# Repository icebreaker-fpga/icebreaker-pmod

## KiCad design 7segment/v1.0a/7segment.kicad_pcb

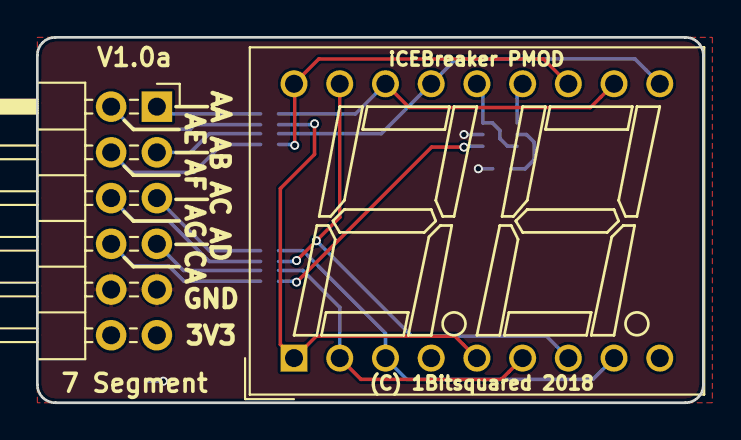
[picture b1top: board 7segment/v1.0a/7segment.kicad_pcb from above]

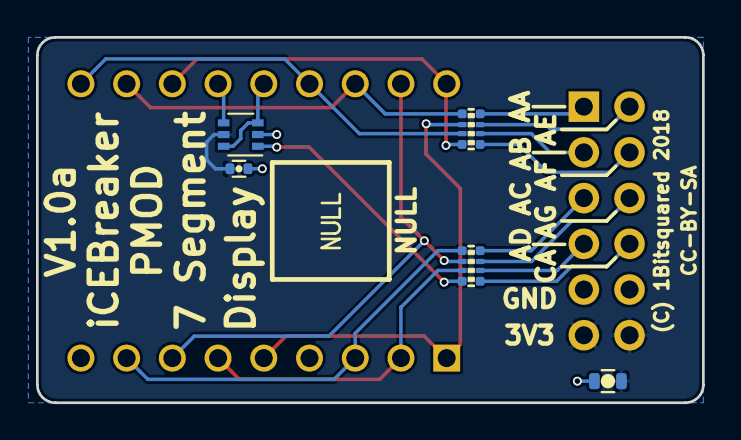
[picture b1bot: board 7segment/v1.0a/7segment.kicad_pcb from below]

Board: 2 copper layers, 37.0 x 20.3 mm, 7 parts (5 on the bottom side), 20 nets.

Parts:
C1: 10u; C_0603
C2: 100n; C_0402
J1: PMOD; PMODHeader_2x06_P2.54mm_Horizontal
R1, R2: 330E; R_Array_Convex_4x0402
U1: LTD-6910HR
U2: NL27WZ14; SOT-363_SC-70-6

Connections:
+3V3: C1.1, C2.1, J1.6, J1.12, U2.5
/AA: J1.1, R2.2
/AAx: R2.1, U1.11, U1.16
/AB: J1.2, R2.6
/ABx: R2.5, U1.10, U1.15
/AC: J1.3, R1.2
/ACx: R1.1, U1.3, U1.8
/AD: J1.4, R1.6
/ADx: R1.5, U1.2, U1.6
/AE: J1.7, R2.4
/AEx: R2.3, U1.1, U1.5
/AF: J1.8, R2.8
/AFx: R2.7, U1.12, U1.18
/AG: J1.9, R1.4
/AGx: R1.3, U1.7, U1.17
/CAT: J1.10, R1.8
/CAT1: U1.14, U2.3, U2.6
/CAT2: U1.13, U2.4
/CATx: R1.7, U2.1
GND: C1.2, C2.2, J1.5, J1.11, U2.2

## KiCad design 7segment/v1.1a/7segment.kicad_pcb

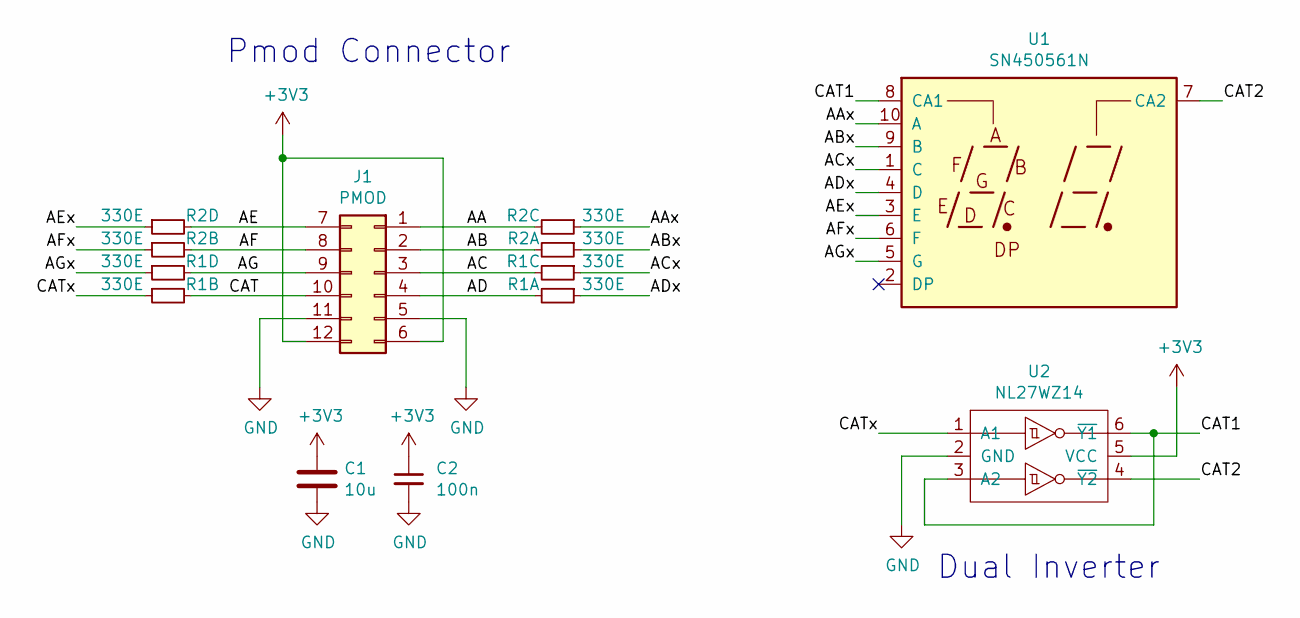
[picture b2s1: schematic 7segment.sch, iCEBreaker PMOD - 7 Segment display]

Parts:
C1: 10u; C_0603
C2: 100n; C_0402
J1: PMOD; PMODHeader_2x06_P2.54mm_Horizontal
R1, R2: 330E; R_Array_Convex_4x0402
U1: SN450561N
U2: NL27WZ14; SOT-363_SC-70-6

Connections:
+3V3: C1.1, C2.1, J1.6, J1.12, U2.5 (VCC)
/AA: J1.1, R2.6
/AAx: R2.5, U1.10 (A)
/AB: J1.2, R2.2
/ABx: R2.1, U1.9 (B)
/AC: J1.3, R1.6
/ACx: R1.5, U1.1 (C)
/AD: J1.4, R1.2
/ADx: R1.1, U1.4 (D)
/AE: J1.7, R2.8
/AEx: R2.7, U1.3 (E)
/AF: J1.8, R2.4
/AFx: R2.3, U1.6 (F)
/AG: J1.9, R1.8
/AGx: R1.7, U1.5 (G)
/CAT: J1.10, R1.4
/CAT1: U1.8 (CA1), U2.3 (A2), U2.6 (~Y1)
/CAT2: U1.7 (CA2), U2.4 (~Y2)
/CATx: R1.3, U2.1 (A1)
GND: C1.2, C2.2, J1.5, J1.11, U2.2 (GND)

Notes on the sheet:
Dual Inverter
Pmod Connector

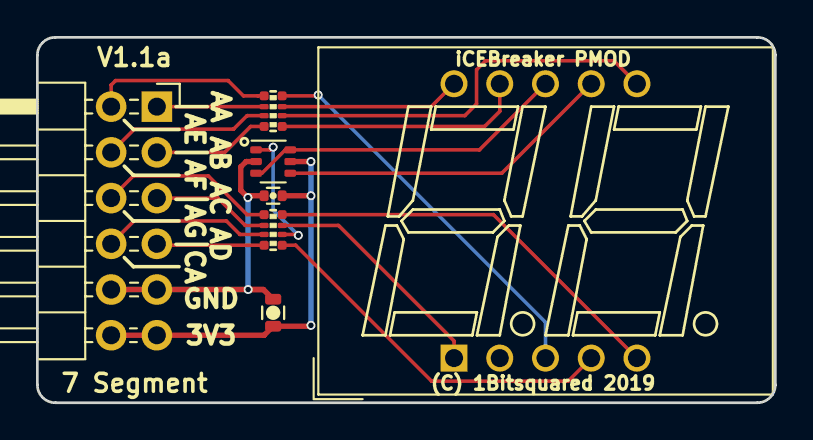
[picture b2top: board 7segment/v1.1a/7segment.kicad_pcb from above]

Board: 2 copper layers, 41.0 x 20.3 mm, 7 parts (0 on the bottom side), 20 nets.

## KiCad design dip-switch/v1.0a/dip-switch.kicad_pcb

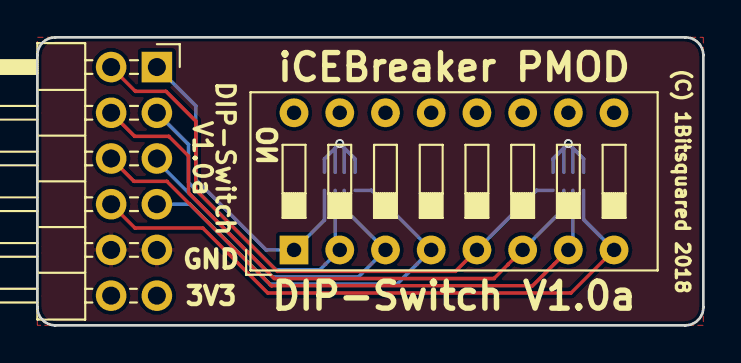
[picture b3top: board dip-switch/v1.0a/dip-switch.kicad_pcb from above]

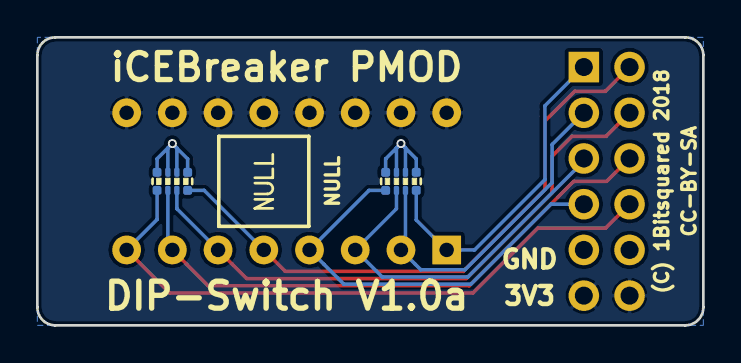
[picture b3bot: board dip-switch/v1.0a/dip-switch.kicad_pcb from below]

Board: 2 copper layers, 37.0 x 16.0 mm, 4 parts (2 on the bottom side), 10 nets.

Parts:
J1: PMOD; PMODHeader_2x06_P2.54mm_Horizontal
R1, R2: 10k; R_Array_Convex_4x0402
SW1: SW_DIP_x08; SW_DIP_SPSTx08_Slide_9.78x22.5mm_W7.62mm_P2.54mm

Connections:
+3V3: J1.6, J1.12, SW1.9, SW1.10, SW1.11, SW1.12, SW1.13, SW1.14, SW1.15, SW1.16
/DIP1: J1.1, R1.2, SW1.1
/DIP2: J1.2, R1.4, SW1.2
/DIP3: J1.3, R1.6, SW1.3
/DIP4: J1.4, R1.8, SW1.4
/DIP5: J1.7, R2.2, SW1.5
/DIP6: J1.8, R2.4, SW1.6
/DIP7: J1.9, R2.6, SW1.7
/DIP8: J1.10, R2.8, SW1.8
GND: J1.5, J1.11, R1.1, R1.3, R1.5, R1.7, R2.1, R2.3, R2.5, R2.7

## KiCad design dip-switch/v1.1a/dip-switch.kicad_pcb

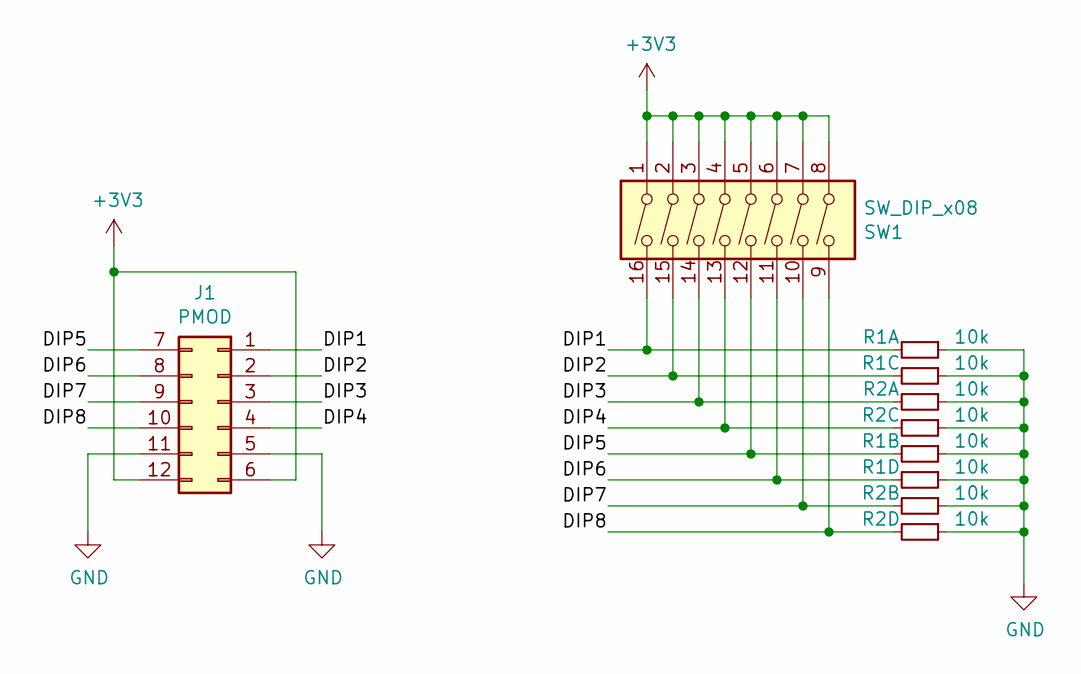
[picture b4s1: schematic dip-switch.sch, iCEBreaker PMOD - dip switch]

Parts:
J1: PMOD; PMODHeader_2x06_P2.54mm_Horizontal
R1, R2: 10k; R_Array_Convex_4x0402
SW1: SW_DIP_x08; SW_DIP_SPSTx08_Slide_9.78x22.5mm_W7.62mm_P2.54mm

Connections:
+3V3: J1.6, J1.12, SW1.1, SW1.2, SW1.3, SW1.4, SW1.5, SW1.6, SW1.7, SW1.8
/DIP1: J1.1, R1.2, SW1.16
/DIP2: J1.2, R1.6, SW1.15
/DIP3: J1.3, R2.2, SW1.14
/DIP4: J1.4, R2.6, SW1.13
/DIP5: J1.7, R1.4, SW1.12
/DIP6: J1.8, R1.8, SW1.11
/DIP7: J1.9, R2.4, SW1.10
/DIP8: J1.10, R2.8, SW1.9
GND: J1.5, J1.11, R1.1, R1.3, R1.5, R1.7, R2.1, R2.3, R2.5, R2.7

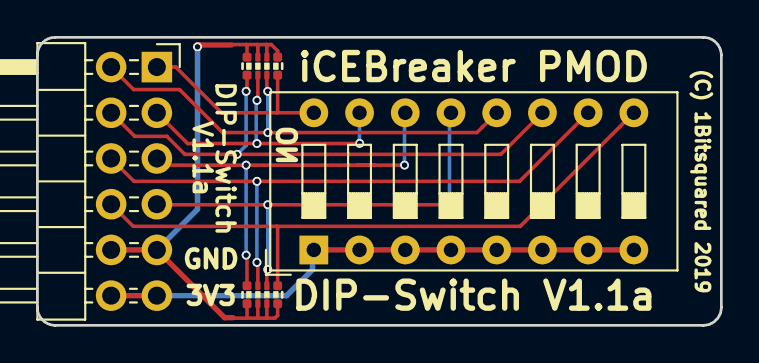
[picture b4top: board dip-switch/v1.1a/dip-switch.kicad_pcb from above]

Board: 2 copper layers, 38.0 x 16.0 mm, 4 parts (0 on the bottom side), 10 nets.

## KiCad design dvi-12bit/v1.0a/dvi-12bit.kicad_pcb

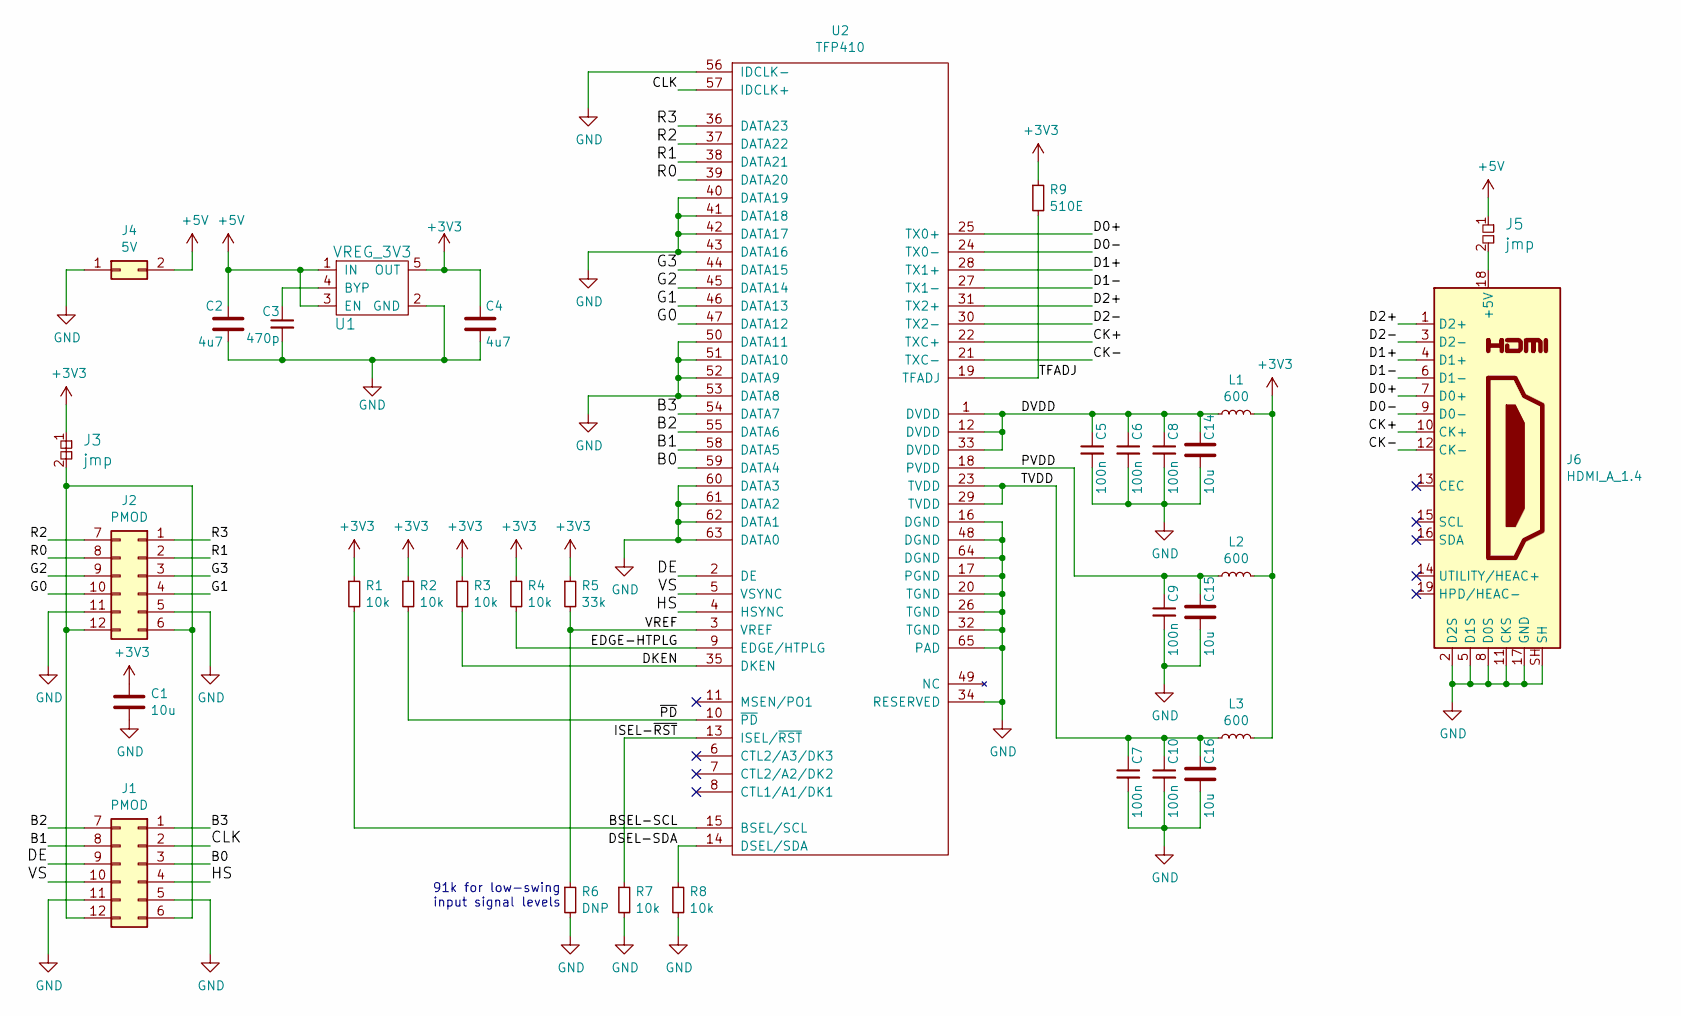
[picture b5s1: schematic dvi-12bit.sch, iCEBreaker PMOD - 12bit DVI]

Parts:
C1, C14, C15, C16: 10u; C_0603
C2, C4: 4u7; C_0603
C3: 470p; C_0402
C5, C6, C7, C8, C9, C10: 100n; C_0402
J1, J2: PMOD; PMODHeader_2x06_P2.54mm_Horizontal
J3: jmp; J_NC_0603_30
J4: 5V; PinHeader_2x01_P2.54mm_Vertical
J5: jmp; J_0603
J6: HDMI_A_1.4; HDMI-10029449-111RLF
L1, L2, L3: 600; L_0402
R1, R2, R3, R4, R7, R8: 10k; R_0402
R5: 33k; R_0402
R6: DNP; R_0402
R9: 510E; R_0402
U1: VREG_3V3; SOT-23-5
U2: TFP410; TQFP-64-1EP_10x10mm_P0.5mm_EP5x5mm

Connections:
+3V3: C1.1, C4.1, J3.1, L1.1, L2.1, L3.1, R1.1, R2.1, R3.1, R4.1, R5.1, R9.1, U1.5 (OUT)
+5V: C2.1, J4.2, J5.1, U1.1 (IN), U1.3 (EN)
/B0: J1.3, U2.59 (DATA4)
/B1: J1.8, U2.58 (DATA5)
/B2: J1.7, U2.55 (DATA6)
/B3: J1.1, U2.54 (DATA7)
/BSEL-SCL: R1.2, U2.15 (BSEL/SCL)
/CK+: J6.10 (CK+), U2.22 (TXC+)
/CK-: J6.12 (CK-), U2.21 (TXC-)
/CLK: J1.2, U2.57 (IDCLK+)
/D0+: J6.7 (D0+), U2.25 (TX0+)
/D0-: J6.9 (D0-), U2.24 (TX0-)
/D1+: J6.4 (D1+), U2.28 (TX1+)
/D1-: J6.6 (D1-), U2.27 (TX1-)
/D2+: J6.1 (D2+), U2.31 (TX2+)
/D2-: J6.3 (D2-), U2.30 (TX2-)
/DE: J1.9, U2.2 (DE)
/DKEN: R3.2, U2.35 (DKEN)
/DSEL-SDA: R8.1, U2.14 (DSEL/SDA)
/DVDD: C5.1, C6.1, C8.1, C14.1, L1.2, U2.1 (DVDD), U2.12 (DVDD), U2.33 (DVDD)
/EDGE-HTPLG: R4.2, U2.9 (EDGE/HTPLG)
/G0: J2.10, U2.47 (DATA12)
/G1: J2.4, U2.46 (DATA13)
/G2: J2.9, U2.45 (DATA14)
/G3: J2.3, U2.44 (DATA15)
/HS: J1.4, U2.4 (HSYNC)
/ISEL-~RST: R7.1, U2.13 (ISEL/~RST)
/PVDD: C9.1, C15.1, L2.2, U2.18 (PVDD)
/R0: J2.8, U2.39 (DATA20)
/R1: J2.2, U2.38 (DATA21)
/R2: J2.7, U2.37 (DATA22)
/R3: J2.1, U2.36 (DATA23)
/TFADJ: R9.2, U2.19 (TFADJ)
/TVDD: C7.1, C10.1, C16.1, L3.2, U2.23 (TVDD), U2.29 (TVDD)
/VREF: R5.2, R6.1, U2.3 (VREF)
/VS: J1.10, U2.5 (VSYNC)
/~PD: R2.2, U2.10 (~PD)
GND: C1.2, C2.2, C3.2, C4.2, C5.2, C6.2, C7.2, C8.2, C9.2, C10.2, C14.2, C15.2, C16.2, J1.5, J1.11, J2.5, J2.11, J4.1, J6.2 (D2S), J6.5 (D1S), J6.8 (D0S), J6.11 (CKS), J6.17 (GND), J6.SH, R6.2, R7.2, R8.2, U1.2 (GND), U2.16 (DGND), U2.17 (PGND), U2.20 (TGND), U2.26 (TGND), U2.32 (TGND), U2.34 (RESERVED), U2.40 (DATA19), U2.41 (DATA18), U2.42 (DATA17), U2.43 (DATA16), U2.48 (DGND), U2.50 (DATA11), U2.51 (DATA10), U2.52 (DATA9), U2.53 (DATA8), U2.56 (IDCLK-), U2.60 (DATA3), U2.61 (DATA2), U2.62 (DATA1), U2.63 (DATA0), U2.64 (DGND), U2.65 (PAD)
unnamed: C3.1, U1.4 (BYP)
unnamed: J1.6, J1.12, J2.6, J2.12, J3.2
unnamed: J5.2, J6.18 (+5V)

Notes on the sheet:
91k for low-swing input signal levels

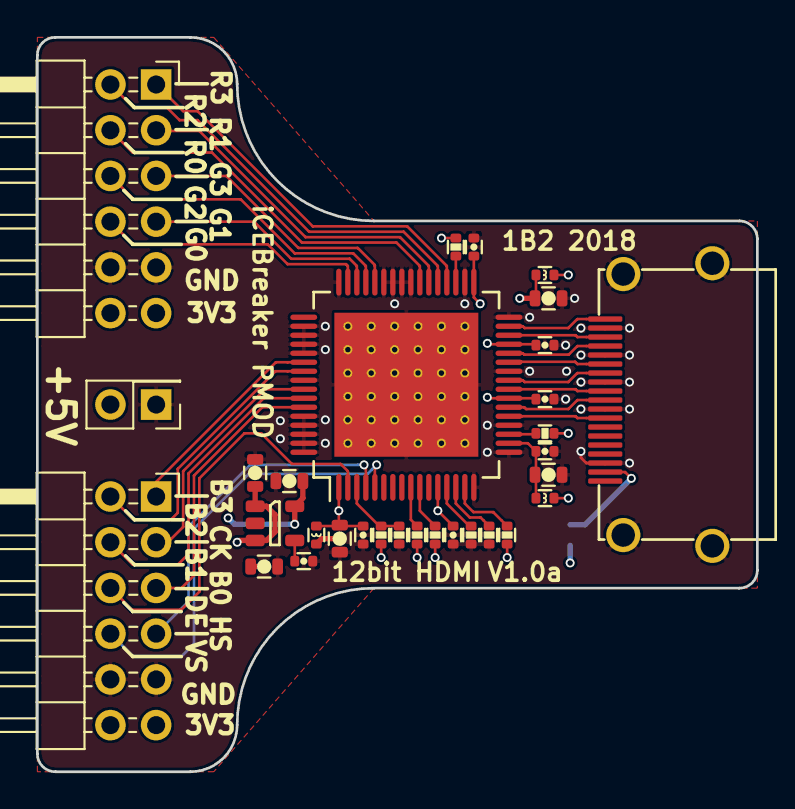
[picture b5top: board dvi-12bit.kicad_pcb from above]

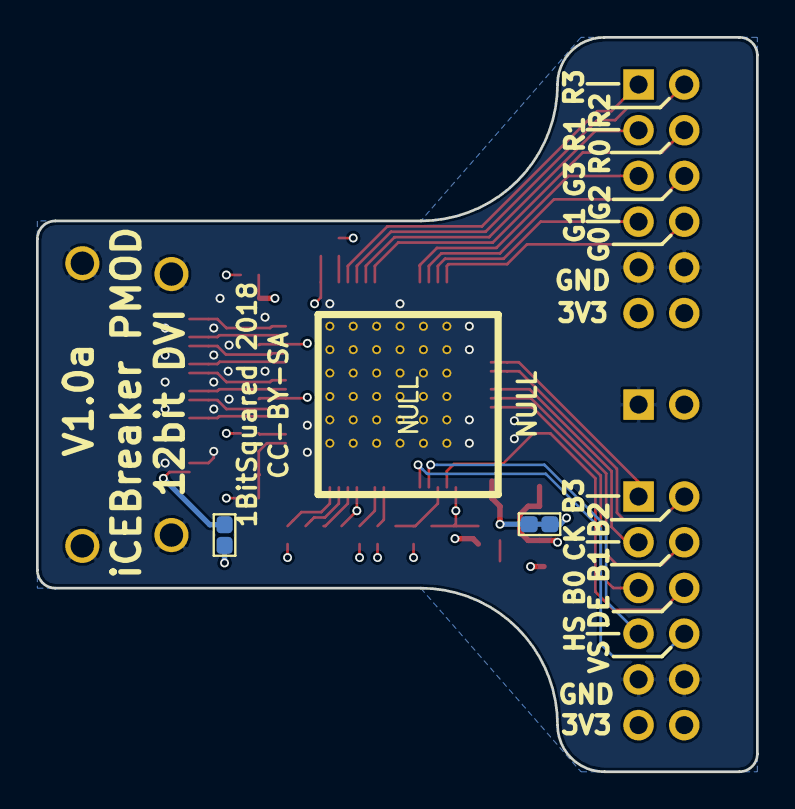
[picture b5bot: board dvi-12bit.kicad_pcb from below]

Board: 4 copper layers, 40.0 x 40.8 mm, 33 parts (2 on the bottom side), 41 nets.

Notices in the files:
7segment/v1.0a/7segment.kicad_pcb:
(C) 2018 Piotr Esden-Tempski
(C) 2018 1BitSquared
License: CC-BY-SA V4.0
CC-BY-SA
7segment/v1.1a/7segment.kicad_pcb:
(C) 2019 Piotr Esden-Tempski
(C) 2019 1BitSquared
dvi-12bit/v1.0b/dvi-12bit.sch:
(C) 2018-2019 Piotr Esden-Tempski
(C) 2018-2019 1BitSquared
dvi-12bit/v1.1b/dvi-12bit.sch:
(C) 2018-2021 Piotr Esden-Tempski
(C) 2018-2021 1BitSquared
